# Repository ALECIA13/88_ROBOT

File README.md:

#Authors
Hlungwani Khanyisa (hlnkha010@myuct.ac.za)
Nyangiwe Someleze (nynsom001@myuct.ac.za)

##PROJECT OBJECTIVE

This is a project for a micro-mouse which is required to detect obstacles in its path. The system is made of four models: Power, Sensor, Motherboard and Processor. The power modules provides power to the whole system. The sensing system behaves like the eyes of the micro-mouse robot to detect the presence of an obstacle in its path. It uses infrared light for obstacle detection. It consists of two circuits, a receiver and an emitter circuit. The emitter circuit emits infrared light in the direction of an obstacle. The receiver circuit detects the emitted light and the output is taken from the receiver and connected to the processor. The processor controls LEDs which indicate obstacle detection. LED ON, means an obstacle is present. LED OFF, means no obstacle present. 

##HOW THE MODULES INTERFACE
The Power module has a connector which interfaces with the motherboard. Similarly with the Sensor module. The output of the Sensor Module transmits data to the Processor and the processor also sends PWM signal to the sensor. 

##STEP BY STEP GUIDE
This repository consists of the datasheets and KiCAD files used for both the Power and Sensor modules.
Connect all the Modules to the Motherboard.
Connect the Sensor Module to the Processor.

##EXPECTED RESULTS
The Processor controls the LEDs to indicate obstacle detection.

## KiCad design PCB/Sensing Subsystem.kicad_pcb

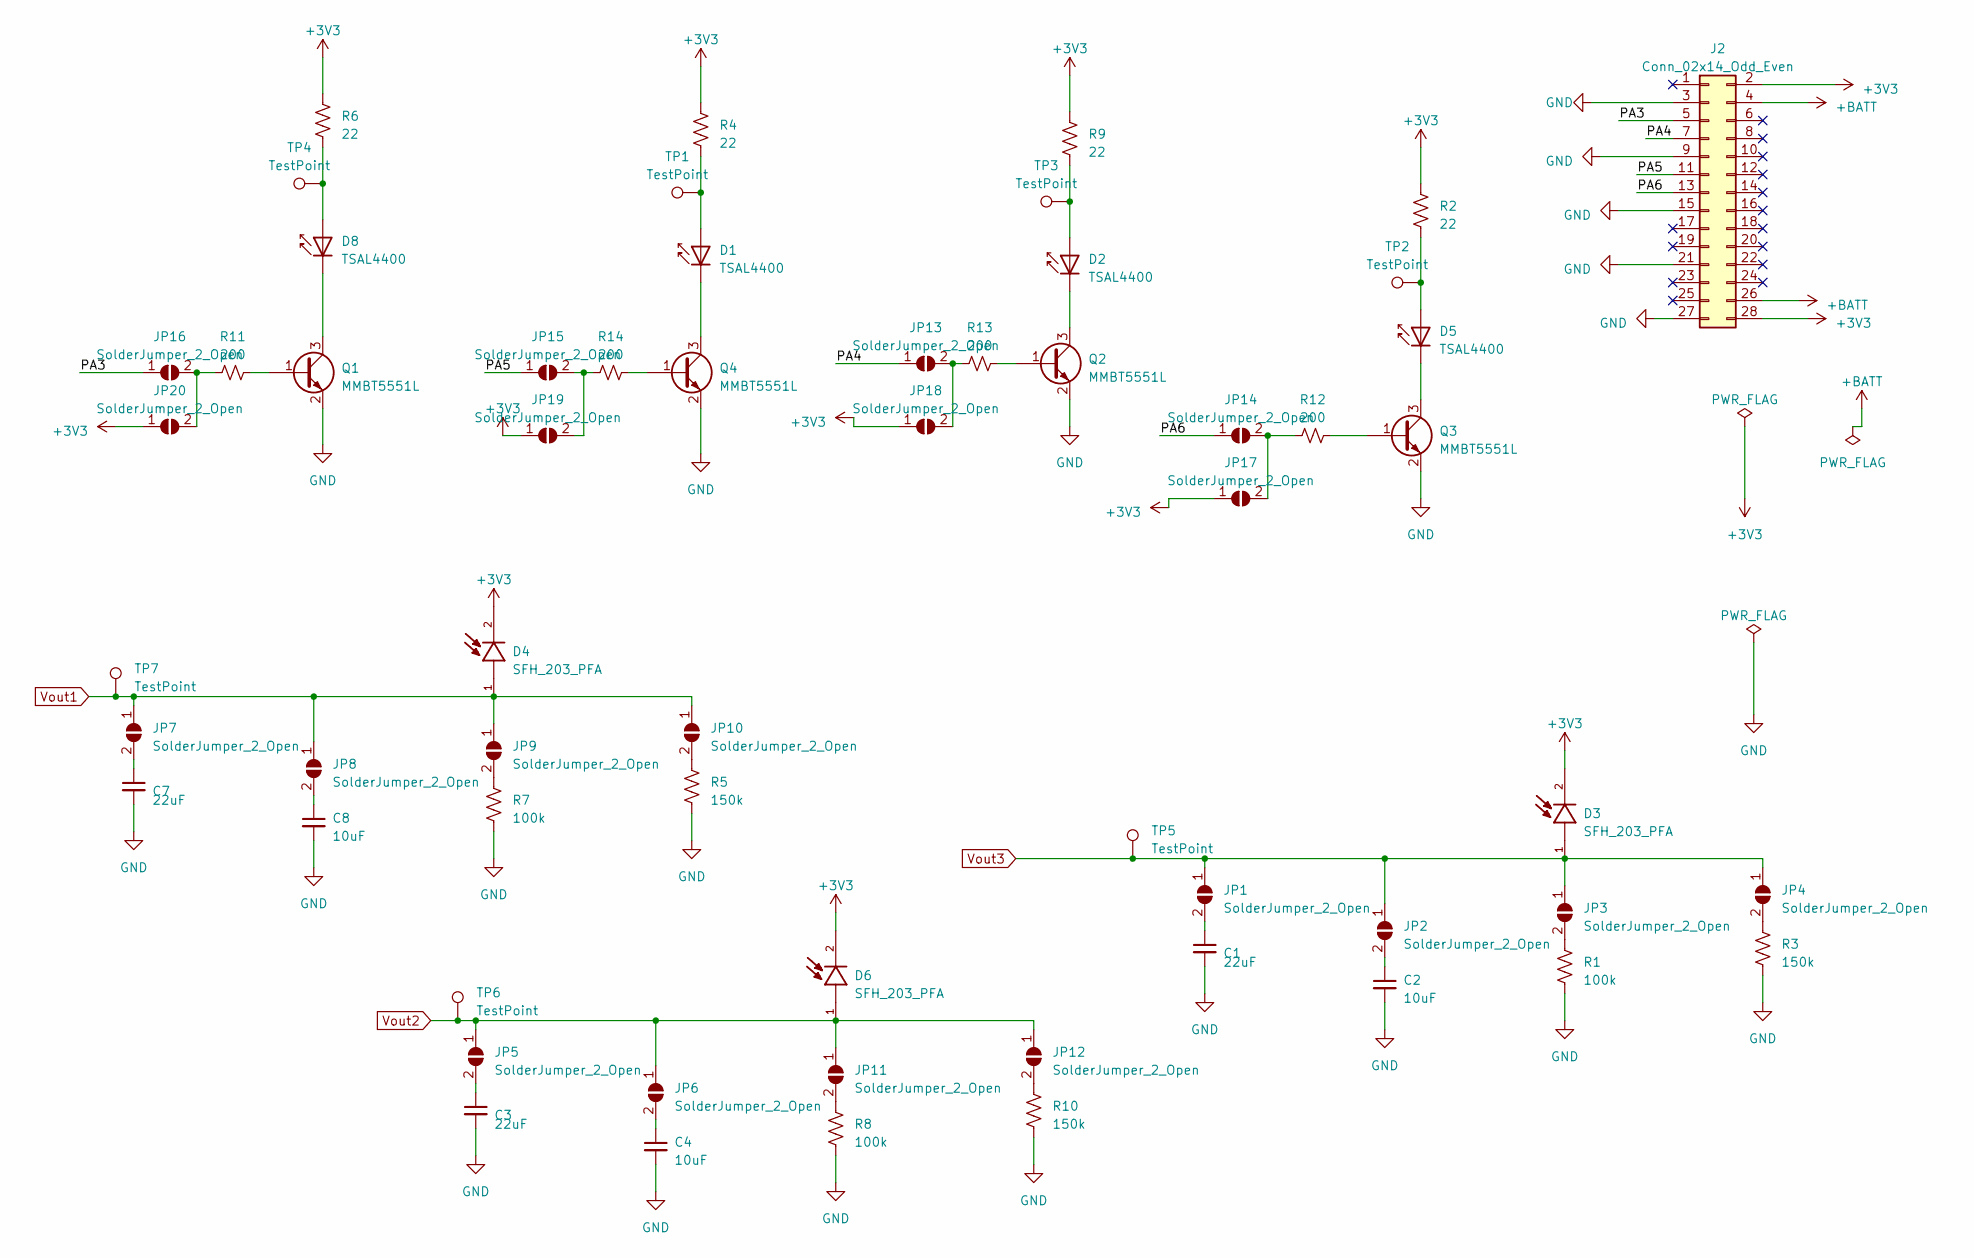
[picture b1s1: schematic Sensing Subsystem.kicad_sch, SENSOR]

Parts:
C1, C3, C7: 22uF; C_1206_3216Metric
C2, C4, C8: 10uF; C_1206_3216Metric
D1, D2, D5, D8: TSAL4400; LED_D5.0mm_Horizontal_O1.27mm_Z3.0mm_IRBlack
D3, D4, D6: SFH_203_PFA; XDCR_SFH_203_PFA; PARTREV 1.3
J2: Conn_02x14_Odd_Even; JST_PHD_B28B-PHDSS_2x14_P2.00mm_Vertical
JP1, JP2, JP3, JP4, JP5, JP6, JP7, JP8, JP9, JP10, JP11, JP12, JP13, JP14, JP15, JP16, JP17, JP18, JP19, JP20: SolderJumper_2_Open; SolderJumper-2_P1.3mm_Open_RoundedPad1.0x1.5mm
Q1, Q2, Q3, Q4: MMBT5551L; SOT-23
R1, R7, R8: 100k; R_0805_2012Metric
R2, R4, R6, R9: 22; R_0805_2012Metric
R3, R5, R10: 150k; R_0805_2012Metric
R11, R12, R13, R14: 200; R_0805_2012Metric
TP1, TP2, TP3, TP4, TP5, TP6, TP7: TestPoint; TestPoint_Pad_D1.0mm

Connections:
+3V3: D3.2, D4.2, D6.2, J2.2, J2.28, JP17.1 (A), JP18.1 (A), JP19.1 (A), JP20.1 (A), R2.1, R4.1, R6.1, R9.1
+BATT: J2.4, J2.26
/PA3: J2.5, JP16.1 (A)
/PA4: J2.7, JP13.1 (A)
/PA5: J2.11, JP15.1 (A)
/PA6: J2.13, JP14.1 (A)
GND: C1.2, C2.2, C3.2, C4.2, C7.2, C8.2, J2.3, J2.9, J2.15, J2.21, J2.27, Q1.2 (E), Q2.2 (E), Q3.2 (E), Q4.2 (E), R1.2, R3.2, R5.2, R7.2, R8.2, R10.2
unnamed: D1.2 (A), R4.2, TP1.1
unnamed: D1.1 (K), Q4.3 (C)
unnamed: D2.2 (A), R9.2, TP3.1
unnamed: D2.1 (K), Q2.3 (C)
unnamed: D5.2 (A), R2.2, TP2.1
unnamed: D5.1 (K), Q3.3 (C)
unnamed: D8.2 (A), R6.2, TP4.1
unnamed: D8.1 (K), Q1.3 (C)
unnamed: C1.1, JP1.2 (B)
unnamed: C2.1, JP2.2 (B)
unnamed: JP3.2 (B), R1.1
unnamed: JP4.2 (B), R3.1
unnamed: C3.1, JP5.2 (B)
unnamed: C4.1, JP6.2 (B)
unnamed: C7.1, JP7.2 (B)
unnamed: C8.1, JP8.2 (B)
unnamed: JP9.2 (B), R7.1
unnamed: JP10.2 (B), R5.1
unnamed: JP11.2 (B), R8.1
unnamed: JP12.2 (B), R10.1
unnamed: JP13.2 (B), JP18.2 (B), R13.1
unnamed: JP14.2 (B), JP17.2 (B), R12.1
unnamed: JP15.2 (B), JP19.2 (B), R14.1
unnamed: JP16.2 (B), JP20.2 (B), R11.1
unnamed: Q1.1 (B), R11.2
unnamed: Q2.1 (B), R13.2
unnamed: Q3.1 (B), R12.2
unnamed: Q4.1 (B), R14.2
Vout1: D4.1, JP7.1 (A), JP8.1 (A), JP9.1 (A), JP10.1 (A), TP7.1
Vout2: D6.1, JP5.1 (A), JP6.1 (A), JP11.1 (A), JP12.1 (A), TP6.1
Vout3: D3.1, JP1.1 (A), JP2.1 (A), JP3.1 (A), JP4.1 (A), TP5.1

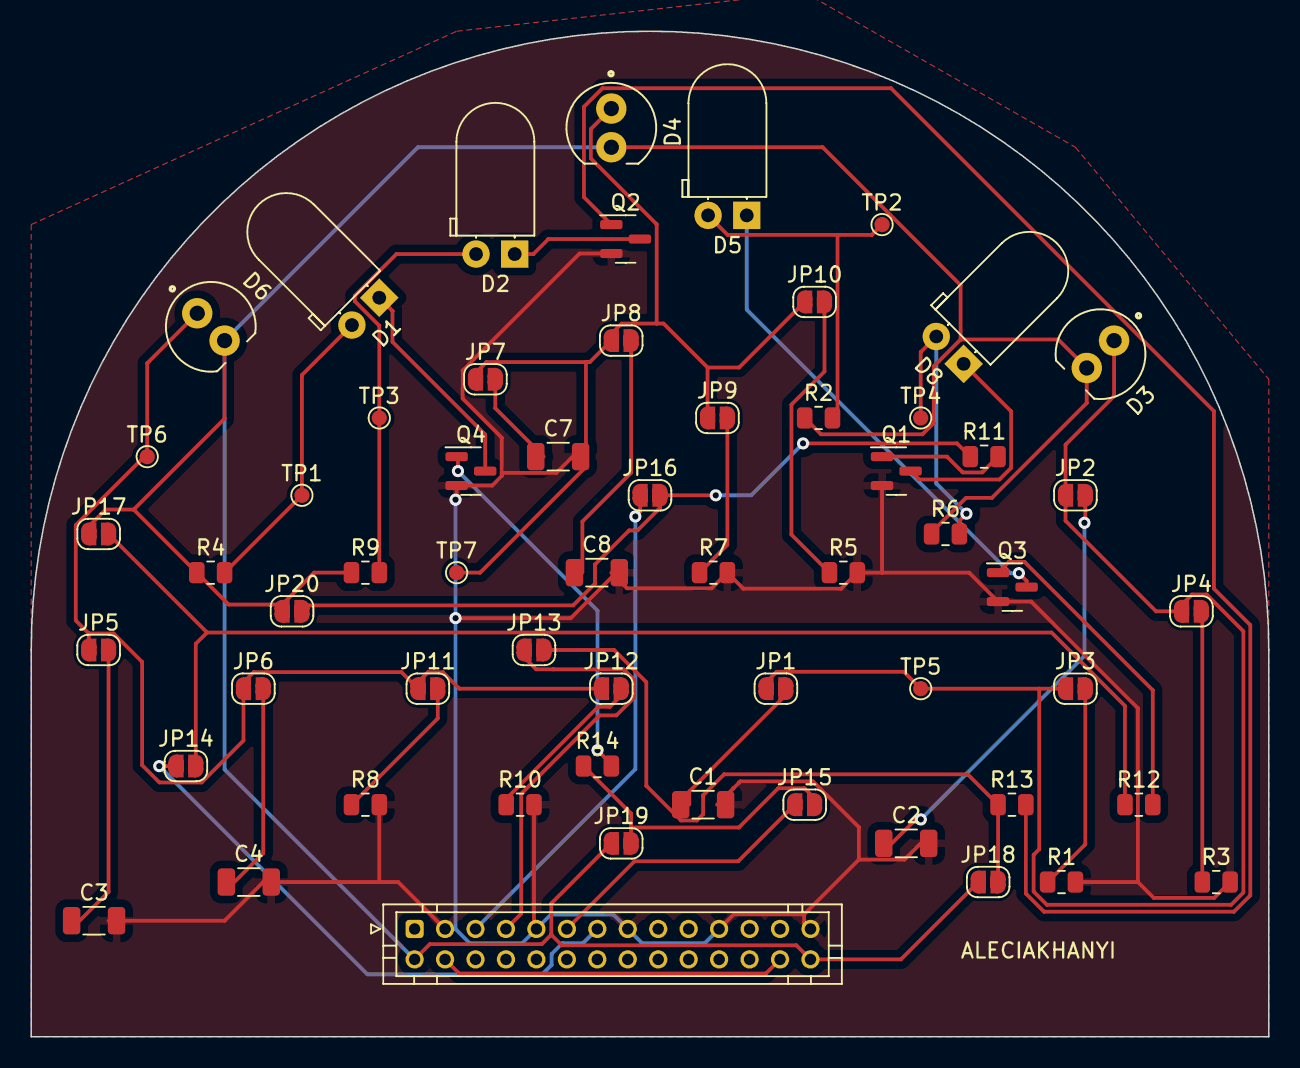
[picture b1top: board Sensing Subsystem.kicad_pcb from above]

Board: 2 copper layers, 81.3 x 66.0 mm, 59 parts (0 on the bottom side), 38 nets.

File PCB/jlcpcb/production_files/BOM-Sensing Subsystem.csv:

Comment,Designator,Footprint,LCSC
100k,"R1,R7,R8",R_0805_2012Metric,C149504
150k,"R10,R3,R5",R_0805_2012Metric,C17470
200,"R11,R12,R13,R14",R_0805_2012Metric,C17540
22,"R2,R4,R6,R9",R_0805_2012Metric,C17561
MMBT5551L,"Q1,Q2,Q3,Q4",SOT-23,C2145
SFH_203_PFA,"D3,D4,D6",XDCR_SFH_203_PFA,C554984
TSAL4400,"D1,D2,D5,D8",LED_D5.0mm_Horizontal_O1.27mm_Z3.0mm_IRBlack,C94135
SolderJumper_2_Open,JP10,SolderJumper-2_P1.3mm_Open_RoundedPad1.0x1.5mm,
22uF,C1,C_1206_3216Metric,
SolderJumper_2_Open,JP3,SolderJumper-2_P1.3mm_Open_RoundedPad1.0x1.5mm,
SolderJumper_2_Open,JP20,SolderJumper-2_P1.3mm_Open_RoundedPad1.0x1.5mm,
TestPoint,TP5,TestPoint_Pad_D1.0mm,
SolderJumper_2_Open,JP11,SolderJumper-2_P1.3mm_Open_RoundedPad1.0x1.5mm,
TestPoint,TP2,TestPoint_Pad_D1.0mm,
SolderJumper_2_Open,JP7,SolderJumper-2_P1.3mm_Open_RoundedPad1.0x1.5mm,
TestPoint,TP7,TestPoint_Pad_D1.0mm,
22uF,C7,C_1206_3216Metric,
SolderJumper_2_Open,JP15,SolderJumper-2_P1.3mm_Open_RoundedPad1.0x1.5mm,
SolderJumper_2_Open,JP19,SolderJumper-2_P1.3mm_Open_RoundedPad1.0x1.5mm,
SolderJumper_2_Open,JP1,SolderJumper-2_P1.3mm_Open_RoundedPad1.0x1.5mm,
SolderJumper_2_Open,JP16,SolderJumper-2_P1.3mm_Open_RoundedPad1.0x1.5mm,
SolderJumper_2_Open,JP8,SolderJumper-2_P1.3mm_Open_RoundedPad1.0x1.5mm,
10uF,C4,C_1206_3216Metric,
SolderJumper_2_Open,JP18,SolderJumper-2_P1.3mm_Open_RoundedPad1.0x1.5mm,
TestPoint,TP4,TestPoint_Pad_D1.0mm,
Conn_02x14_Odd_Even,J2,JST_PHD_B28B-PHDSS_2x14_P2.00mm_Vertical,
10uF,C8,C_1206_3216Metric,
SolderJumper_2_Open,JP17,SolderJumper-2_P1.3mm_Open_RoundedPad1.0x1.5mm,
SolderJumper_2_Open,JP13,SolderJumper-2_P1.3mm_Open_RoundedPad1.0x1.5mm,
TestPoint,TP6,TestPoint_Pad_D1.0mm,
TestPoint,TP1,TestPoint_Pad_D1.0mm,
SolderJumper_2_Open,JP14,SolderJumper-2_P1.3mm_Open_RoundedPad1.0x1.5mm,
SolderJumper_2_Open,JP4,SolderJumper-2_P1.3mm_Open_RoundedPad1.0x1.5mm,
TestPoint,TP3,TestPoint_Pad_D1.0mm,
SolderJumper_2_Open,JP9,SolderJumper-2_P1.3mm_Open_RoundedPad1.0x1.5mm,
SolderJumper_2_Open,JP5,SolderJumper-2_P1.3mm_Open_RoundedPad1.0x1.5mm,
10uF,C2,C_1206_3216Metric,
22uF,C3,C_1206_3216Metric,
SolderJumper_2_Open,JP2,SolderJumper-2_P1.3mm_Open_RoundedPad1.0x1.5mm,
SolderJumper_2_Open,JP12,SolderJumper-2_P1.3mm_Open_RoundedPad1.0x1.5mm,
SolderJumper_2_Open,JP6,SolderJumper-2_P1.3mm_Open_RoundedPad1.0x1.5mm,

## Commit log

2024-03-21 Update README.md
    Requirements and specifications to help understand what is required of me.
2024-03-21 Update README.md
    Just practice
2024-03-21 Update README.md
    main...
2024-03-30 Added the PCB and datasheets
2024-04-21 Update README.md
    Project description and step by step guide on how to use the project.
2024-04-21 Create test
